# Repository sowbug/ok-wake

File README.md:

OK Wake
=======

[OK Wake](http://www.sowbug.com/ok-wake) is a device that lets pre-literate kids know it's OK to get out of bed.

Copyright © 2012 Mike Tsao.

This project started with a lunchtime conversation with a friend whose kids are too young to read, but not too young to get out of bed at the crack of dawn and wake up their parents. We wondered whether a little blinking light would be a satisfactory signal to keep the kids in bed until the designated hour.

Thus was born the OK Wake. It divides the day into three sections: night, twilight, and dawn. Most of the 24-hour cycle is night, and the device does nothing. If wake-up time is 6am, then twilight would start at 5:30am with a slow red blink, gradually increasing in frequency until dawn at 6am, when the blink changes to a green “breathing” blink. Dawn continues for 10 minutes, and then night resumes.

While working on the feature set, I had some very intricate ideas for dealing with Daylight Saving Time. Either I’d just handle it (meaning the kids would be confused by the abrupt shift twice a year), or I’d do a gradual shift in the week or so leading up to the time change. It got complicated, especially when I thought about the case where the family traveled to a different timezone. I finally decided I was overthinking the problem, and added a button. Pressing the button sets the alarm to 12 hours from the current time (e.g., press at 6pm to wake at 6am). I want to call this the antipode, as it’s the opposite point on a circular clock, but I think I’m misusing that term. I think the 6pm/6am solution is simple and elegant; as a parent I know kids want to wake up around 6am, and 6pm is right around the time parents are thinking they’d be totally OK with the kids going to bed right now.

The circuit is based on an ATtiny25 microcontroller and a Philips/NXP PCF8523 real-time clock chip. I chose the ‘8523 for two reasons: first, it is not the Maxim DS1307, which is shockingly expensive for a chip that’s basically a digital counter; and second, because it uses I2C, which I wanted to learn about.

Early in the design phase, I concluded that picking the ‘8523 eliminated my current favorite AVR, the ATtiny13a, because that chip didn’t support I2C. But as I later learned, the ATtiny25 doesn’t really support I2C either, except to the extent that it has a USART that can be tricked into assisting with I2C bit-banging. In the end I didn’t even use the USART anyway, instead relying on a fantastic small I2C library that uses two GPIO pins. But I’m happy I had the ‘25 rather than the ‘13a, because I used up about 1,800 of the 2KB program space, and wouldn’t have had much fun trying to squeeze that into the 1KB space of the ‘13a.

The firmware took one weekend day and two nights to write, which felt like a long time for a fairly simple set of features. I started out using an Arduino as the hardware platform, which was marginally useful for getting up and running, but eventually I threw out all that code when rewriting for the ‘25. The most frustrating part by far was dealing with the packed BCD (binary-coded decimal) that appears to be commonplace with RTC chips. I did just enough time math that I had to write bcd add/subtract routines (fortunately there are canonical bit-twiddling solutions on the web), and BCD-to-time-aware-decimal conversion routines. Unit tests helped a lot here.

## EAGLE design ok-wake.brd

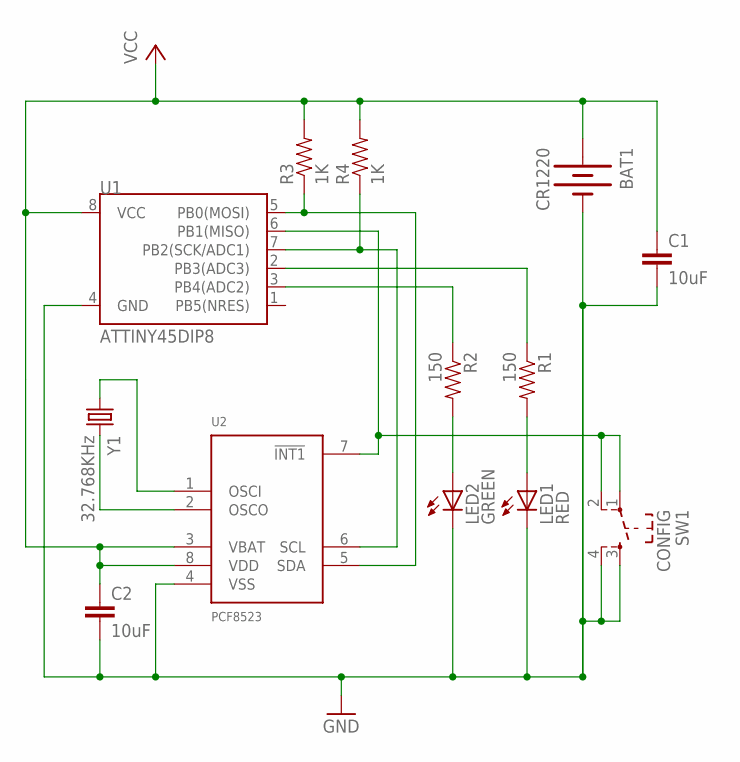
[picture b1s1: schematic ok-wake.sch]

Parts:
BAT1: CR1220; BATTCON_12MM
C1, C2: 10uF; 1206
LED1: RED; CHIP-LED0805
LED2: GREEN; CHIP-LED0805
R1, R2: 150; 0805
R3, R4: 1K; 0805
SW1: CONFIG; SW_TACT_SMALL
U1: ATTINY45DIP8; DIP08
U2: PCF8523; SO8
Y1: 32.768KHz; CRYSTAL-32KHZ-SMD

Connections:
!INT1: SW1.1, SW1.2, U1.6 (PB1(MISO)), U2.7 (!INT1)
GND: BAT1.GND (-), C1.2, C2.2, LED1.C, LED2.C, SW1.3, SW1.4, U1.4 (GND), U2.4 (VSS)
LED1-LO: LED1.A, R1.2
LED1-OUT: R1.1, U1.2 (PB3(ADC3))
LED2-LO: LED2.A, R2.2
LED2-OUT: R2.1, U1.3 (PB4(ADC2))
OSCI: U2.1 (OSCI), Y1.X1 (1)
OSCO: U2.2 (OSCO), Y1.X2 (2)
SCL/SCK: R4.1, U1.7 (PB2(SCK/ADC1)), U2.6 (SCL)
SDA/MOSI: R3.1, U1.5 (PB0(MOSI)), U2.5 (SDA)
VCC: BAT1.PWR@1 (+), C1.1, C2.1, R3.2, R4.2, U1.8 (VCC), U2.3 (VBAT), U2.8 (VDD)

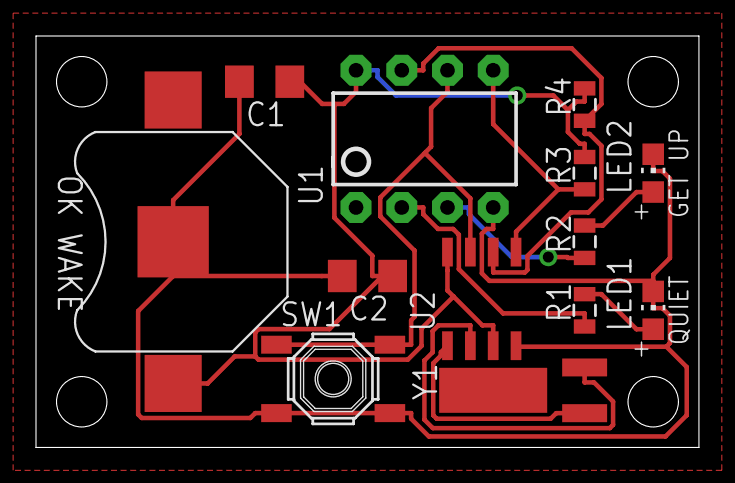
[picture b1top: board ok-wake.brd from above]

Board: 2 copper layers, 36.8 x 22.9 mm, 13 parts (0 on the bottom side), 11 nets.

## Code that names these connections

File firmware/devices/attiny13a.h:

/*
 * OK Wake
 * https://github.com/sowbug/ok-wake/
 *
 */

// Function Tiny 328 Arduino
// Quiet    PB4  PB4 10
// Wake     PB3  PB2 12
// Button   PB1  PB0  8
// SCL      PB2  PC5 A5
// SDA      PB0  PC4 A4

#define QUIET _BV(PB4)
#define QUIET_DD _BV(DDB4)
#define WAKE _BV(PB3)
#define WAKE_DD _BV(DDB3)

#define BUTTON _BV(PB1)
#define BUTTON_DD _BV(DDB1)
#define BUTTON_INT _BV(INT0)

#define LED_PORT PORTB
#define BUTTON_PORT PORTB
#define LED_DDR DDRB
#define BUTTON_DDR DDRB
#define BUTTON_PIN PINB

#define SCL _BV(PB2)
#define SCL_DD _BV(DDB2)
#define SDA _BV(PB0)
#define SDA_DD _BV(DDB0)

static int is_button_pressed() {
  return !(PINB & BUTTON);
}

static void init_power_reduction_register() {
  PRR = _BV(PRADC) | _BV(PRTIM0);  // All peripherals off.
}

static void enable_pin_interrupts() {
  MCUCR = _BV(ISC01);  // The falling edge of INT0 generates an interrupt.
  GIMSK = BUTTON_INT;  // Enable INT0 interrupt.
}

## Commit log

2012-04-15 New.
2012-05-02 Skeleton firmware.
2012-05-06 A checkpoint nearing working firmware on 328p test version.
2012-05-06 Got rid of TODOs.
2012-05-07 Checkpoint.
2012-05-07 Bunch of ATtiny25 work. Not working.
2012-05-07 Fixed bug (no interrupts in interrupt handler). Might be working.
2012-05-07 Clear AF, too.
2012-05-07 Reformatting, and maybe fixed a boundary condition.
2012-05-08 About 1,000 bugfixes.
2012-05-08 Added .orig for astyle.
2012-05-08 astyle.
2012-05-08 Formatting.
2012-05-08 Rearrange to avoid forward declarations.
2012-05-08 Formatting, again.
2012-05-08 Got rid of '328 support. More optimizations.
    http://www.tty1.net/blog/2008-04-29-avr-gcc-optimisations_en.html
2012-05-08 Checkpoint - BCD work. Broken.
2012-05-08 Another broken checkpoint.
2012-05-08 Gave up on shift-based math.
2012-05-09 Nit refactoring.
2012-05-09 Switch over to Peter Fleury's I2C Master library.
2012-05-09 Use block i2c and eeprom access.
2012-05-09 Fix EEMEM reorganization.
2012-05-09 Fixed an argument transposition error.
2012-05-09 Whoops.
2012-05-09 Nicer twilight behavior.
2012-05-09 Cleanup. Fixed a likely failure-to-power-down bug in power_down().
2012-05-09 Express time in UTC.
2012-05-09 More datasheets.
2012-05-10 Fix comment.
2012-05-10 Adjust dawn to be longer.
2013-07-09 Fixed a renaming error.

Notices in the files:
parts and their libraries:
SparkFun: Licensing: CC v3.0 Share-Alike You are welcome to use this library for commercial purposes.
